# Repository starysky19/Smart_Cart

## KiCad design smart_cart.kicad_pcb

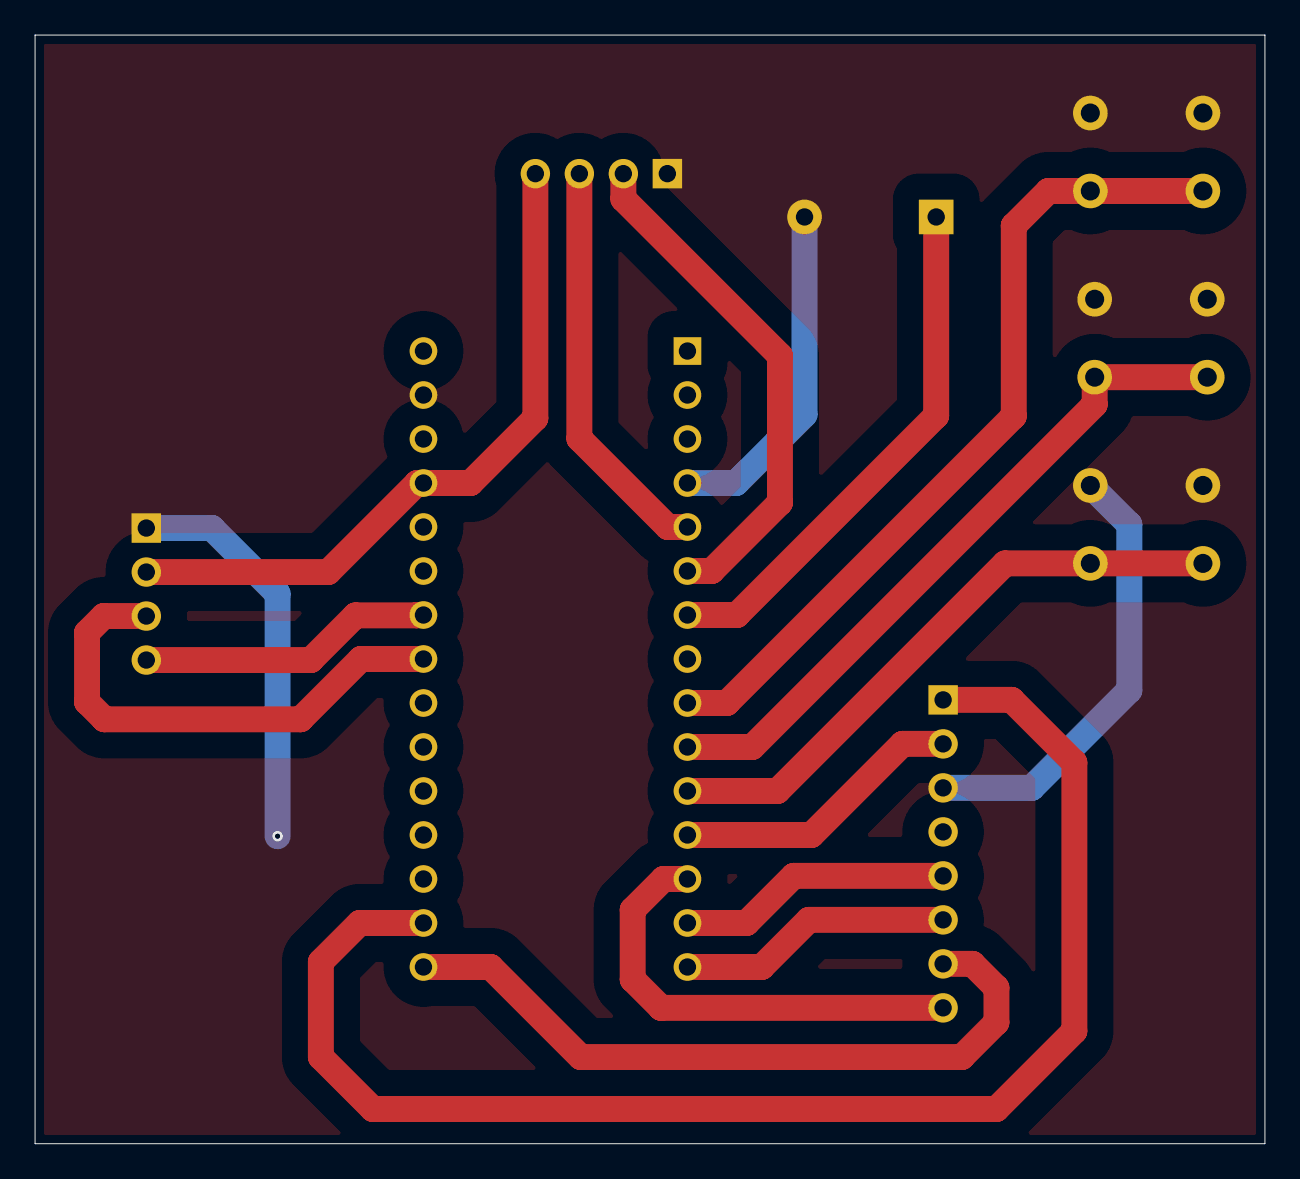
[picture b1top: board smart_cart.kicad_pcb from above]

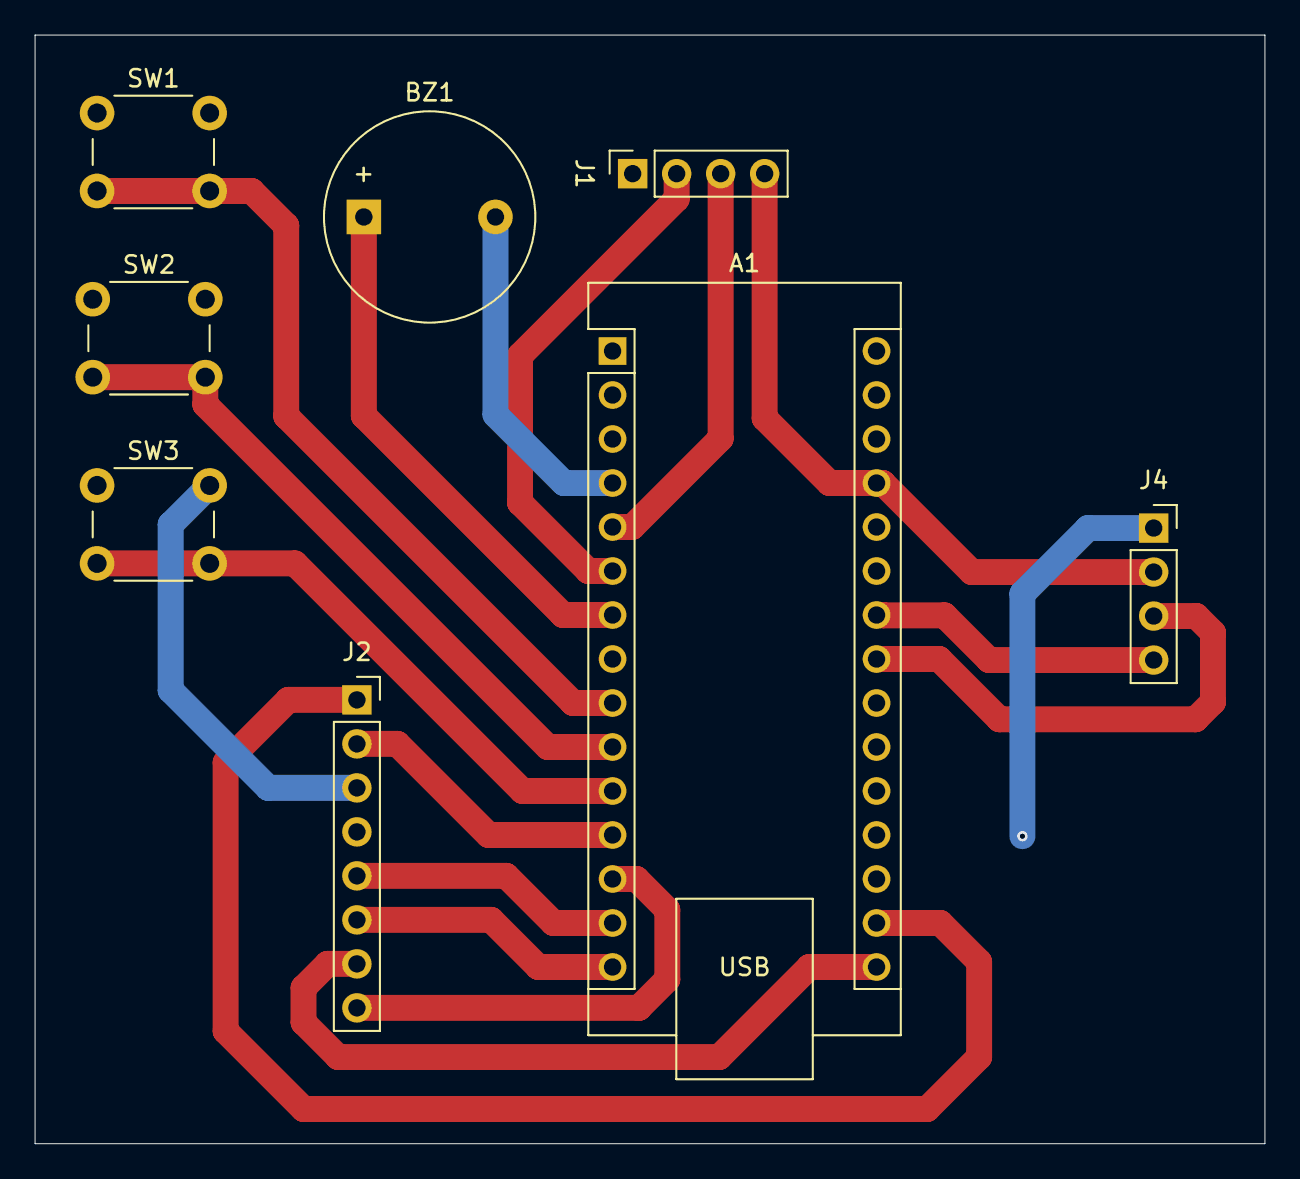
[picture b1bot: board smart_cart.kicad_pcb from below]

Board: 2 copper layers, 71.0 x 64.0 mm, 8 parts (8 on the bottom side), 16 nets.

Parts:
A1: Arduino_Nano_v3.x; Arduino_Nano
BZ1: Buzzer; Buzzer_12x9.5RM7.6
J1: HX711; PinSocket_1x04_P2.54mm_Vertical
J2: RC522; PinSocket_1x08_P2.54mm_Vertical
J4: I2C converter; PinSocket_1x04_P2.54mm_Vertical
SW1, SW2, SW3: SW_Push; SW_PUSH_6mm

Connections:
+3.3V: A1.17 (3V3), J2.1
+5V: A1.27 (+5V), J1.4, J4.2
A4: A1.23 (A4), J4.3
A5: A1.24 (A5), J4.4
D2: A1.5 (D2), J1.3
D3: A1.6 (D3), J1.2
GND: A1.4 (GND), A1.29 (GND), BZ1.2 (-), J1.1, J2.3, J4.1, SW1.1, SW2.1, SW3.1
MISO: A1.14 (D11), J2.5
MOSI: A1.15 (D12), J2.6
unnamed: A1.7 (D4), BZ1.1 (+)
unnamed: A1.9 (D6), SW1.2
unnamed: A1.10 (D7), SW2.2
unnamed: A1.11 (D8), SW3.2
RST: A1.12 (D9), J2.2
SCK: A1.16 (D13), J2.7
SDA: A1.13 (D10), J2.8
